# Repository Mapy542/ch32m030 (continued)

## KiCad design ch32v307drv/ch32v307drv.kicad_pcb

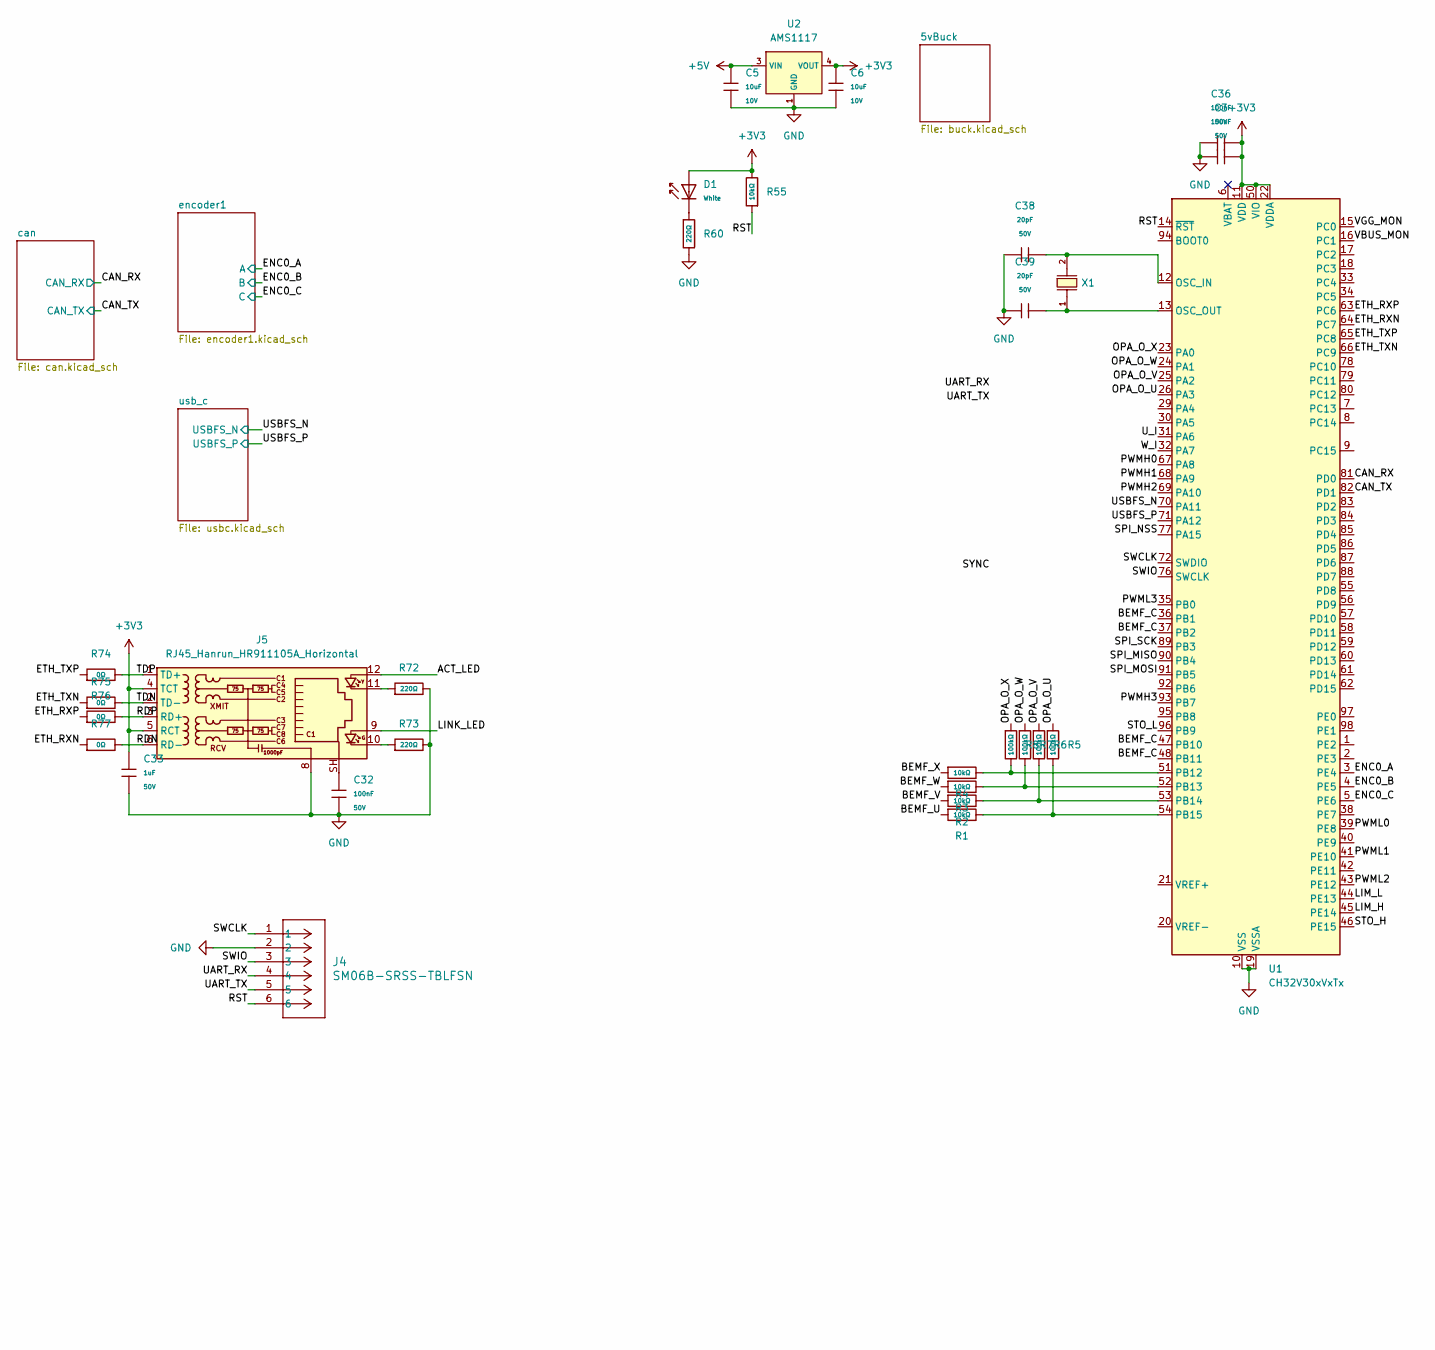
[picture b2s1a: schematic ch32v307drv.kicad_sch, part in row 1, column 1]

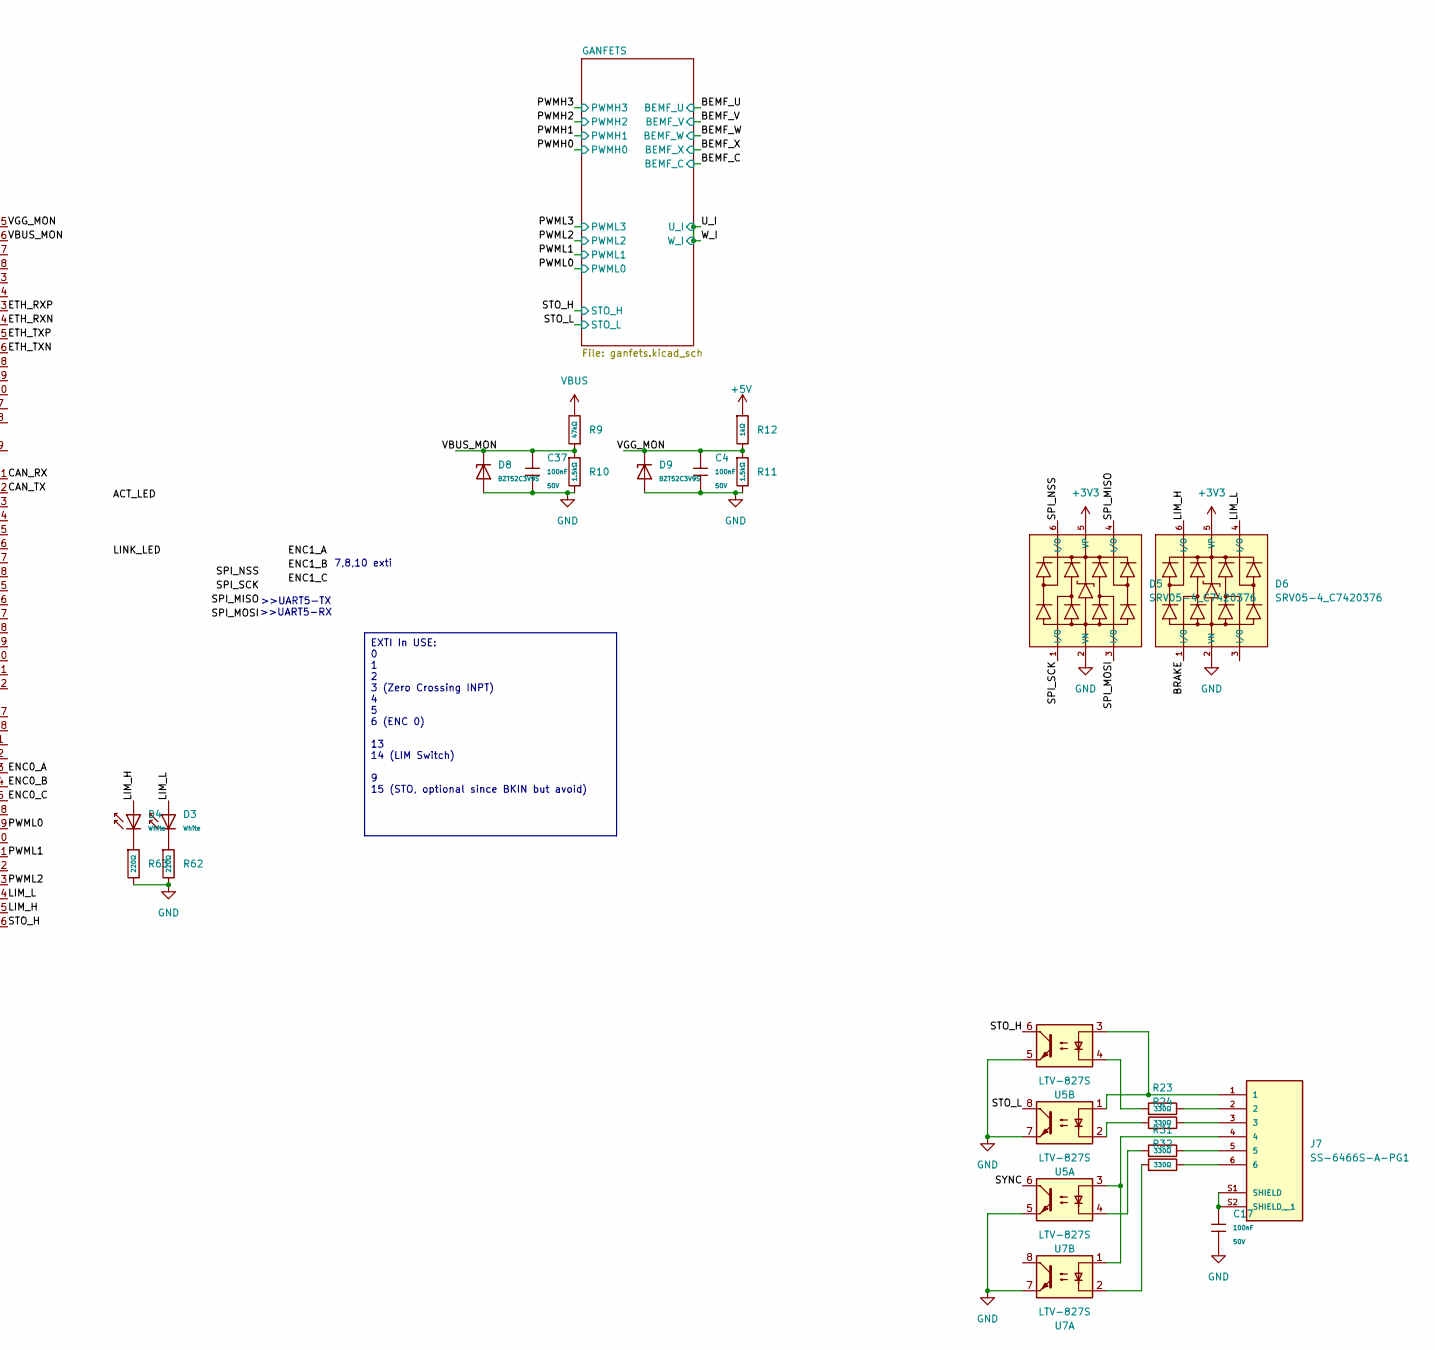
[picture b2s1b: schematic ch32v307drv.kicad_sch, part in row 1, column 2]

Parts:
C3, C4, C36, C37: 100nF; C_0603; Voltage Rated 50V; Tolerance ±10%; Part CC0603KRX7R9BB104; LCSC C14663
C5, C6: 10uF; C_0603; Voltage Rated 10V; Tolerance ±10%; Part CL10A106KP8NNNC; LCSC C19702
C17, C32: 100nF; C_1206; Voltage Rated 50V; Tolerance ±10%; Part CL31B104KBCNNNC; LCSC C24497
C33: 1uF; C_0603; Voltage Rated 50V; Tolerance ±10%; Part CL10A105KB8NNNC; LCSC C15849
C38, C39: 20pF; C_0402; Voltage Rated 50V; Tolerance ±5%; Part 0402CG200J500NT; LCSC C1554
D1, D3, D4: White; D_0603; Part KT-0603W; LCSC C2290
D5, D6: SRV05-4_C7420376; SOT-23-6_L2.9-W1.6-P0.95-LS2.8-BL-1; Breakdown Voltage (Vbr) 6V; Clamping Voltage@Ipp 12.5V; Part SRV05-4; LCSC C7420376
D8, D9: BZT52C3V9S; D_SOD-323; Part BZT52C3V9S; LCSC C22375299
J4: SM06B-SRSS-TBLFSN; CONN_SM06B-SRSS-TB_JST
J5: RJ45_Hanrun_HR911105A_Horizontal
J7: SS-6466S-A-PG1; BEL_SS-6466S-A-PG1; PARTREV A5
R1, R2, R3, R4, R55: 10kΩ; R_0603; Overload Voltage (Max) 75V; Tolerance ±1%; Part 0603WAF1002T5E; LCSC C25804
R5, R6, R7, R8: 100kΩ; R_0603; Overload Voltage (Max) 75V; Tolerance ±1%; Part 0603WAF1003T5E; LCSC C25803
R9: 47kΩ; R_0603; Overload Voltage (Max) 75V; Tolerance ±1%; Part 0603WAF4702T5E; LCSC C25819
R10, R11: 1.5kΩ; R_0603; Overload Voltage (Max) 75V; Tolerance ±1%; Part 0603WAF1501T5E; LCSC C22843
R12: 1kΩ; R_0603; Overload Voltage (Max) 75V; Tolerance ±1%; Part 0603WAF1001T5E; LCSC C21190
R23, R24, R31, R32: 330Ω; R_0603; Overload Voltage (Max) 75V; Tolerance ±1%; Part 0603WAF3300T5E; LCSC C23138
R60, R62, R63, R72, R73: 220Ω; R_0603; Overload Voltage (Max) 75V; Tolerance ±1%; Part 0603WAF2200T5E; LCSC C22962
R74, R75, R76, R77: 0Ω; R_0603; Overload Voltage (Max) 75V; Tolerance ±1%; Part 0603WAF0000T5E; LCSC C21189
U1: CH32V30xVxTx; LQFP-100_14x14mm_P0.5mm
U2: AMS1117; SOT-223-3_L6.5-W3.4-P2.30-LS7.0-BR; Output Voltage 3.3V; Dropout Voltage 1.3V@(800mA); Part AMS1117-3.3; LCSC C6186
U5, U7: LTV-827S; SMDIP-8_W9.53mm
X1: X50328MSB2GI; CRYSTAL-SMD_L5.0-W3.2; Frequency Tolerance ±10ppm; Part X50328MSB2GI; LCSC C115962

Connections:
+3V3: C3.2, C6.1, C33.1, C36.2, D1.2, D5.5 (VP), D6.5 (VP), J5.4 (TCT), J5.5 (RCT), R55.2, U1.11 (VDD), U1.22 (VDDA), U1.28 (VDD), U1.50 (VIO), U1.75 (VDD), U1.100 (VIO), U2.2 (VOUT), U2.4 (VOUT); also elsewhere on the board
+5V: C5.1, R12.1, U2.3 (VIN); also elsewhere on the board
/ACT_LED: J5.12
/BEMF_C: U1.36 (PB1), U1.37 (PB2), U1.47 (PB10), U1.48 (PB11); also elsewhere on the board
/BEMF_U: R1.1; also elsewhere on the board
/BEMF_V: R2.1; also elsewhere on the board
/BEMF_W: R3.1; also elsewhere on the board
/BEMF_X: R4.1; also elsewhere on the board
/BRAKE: D6.1 (I/O)
/CAN_RX: U1.81 (PD0); also elsewhere on the board
/CAN_TX: U1.82 (PD1); also elsewhere on the board
/ENC0_A: U1.3 (PE4); also elsewhere on the board
/ENC0_B: U1.4 (PE5); also elsewhere on the board
/ENC0_C: U1.5 (PE6); also elsewhere on the board
/ETH_RXN: R77.1, U1.64 (PC7)
/ETH_RXP: R76.1, U1.63 (PC6)
/ETH_TXN: R75.1, U1.66 (PC9)
/ETH_TXP: R74.1, U1.65 (PC8)
/LIM_H: D4.2, D6.6 (I/O), U1.45 (PE14)
/LIM_L: D3.2, D6.4 (I/O), U1.44 (PE13)
/LINK_LED: J5.9
/OPA_O_U: R5.1, U1.26 (PA3)
/OPA_O_V: R6.1, U1.25 (PA2)
/OPA_O_W: R7.1, U1.24 (PA1)
/OPA_O_X: R8.1, U1.23 (PA0)
/PWMH0: U1.67 (PA8); also elsewhere on the board
/PWMH1: U1.68 (PA9); also elsewhere on the board
/PWMH2: U1.69 (PA10); also elsewhere on the board
/PWMH3: U1.93 (PB7); also elsewhere on the board
/PWML0: U1.39 (PE8); also elsewhere on the board
/PWML1: U1.41 (PE10); also elsewhere on the board
/PWML2: U1.43 (PE12); also elsewhere on the board
/PWML3: U1.35 (PB0); also elsewhere on the board
/RDN: J5.6 (RD-), R77.2
/RDP: J5.3 (RD+), R76.2
/RST: J4.6, R55.1, U1.14 (~RST)
/SPI_MISO: D5.4 (I/O), U1.90 (PB4)
/SPI_MOSI: D5.3 (I/O), U1.91 (PB5)
/SPI_NSS: D5.6 (I/O), U1.77 (PA15)
/SPI_SCK: D5.1 (I/O), U1.89 (PB3)
/STO_H: U1.46 (PE15), U5.6; also elsewhere on the board
/STO_L: U1.96 (PB9), U5.8; also elsewhere on the board
/SWCLK: J4.1, U1.72 (SWDIO)
/SWIO: J4.3, U1.76 (SWCLK)
/SYNC: U7.6
/TDN: J5.2 (TD-), R75.2
/TDP: J5.1 (TD+), R74.2
/UART_RX: J4.4
/UART_TX: J4.5
/USBFS_N: U1.70 (PA11); also elsewhere on the board
/USBFS_P: U1.71 (PA12); also elsewhere on the board
/U_I: U1.31 (PA6), U1.32 (PA7); also elsewhere on the board
/VBUS_MON: C37.2, D8.1, R9.1, R10.1, U1.16 (PC1)
/VGG_MON: C4.2, D9.1, R11.1, R12.2, U1.15 (PC0)
GND: C3.1, C4.1, C5.2, C6.2, C17.2, C32.2, C33.2, C36.1, C37.1, C38.1, C39.1, D5.2 (VN), D6.2 (VN), D8.2, D9.2, J4.2, J5.8, R10.2, R11.2, R60.2, R62.2, R63.2, R72.2, R73.2, U1.10 (VSS), U1.19 (VSSA), U1.27 (VSS), U1.49 (VSS), U1.74 (VSS), U1.99 (VSS), U2.1 (GND), U5.5, U5.7, U7.5, U7.7; also elsewhere on the board
unnamed: C32.1, J5.SH
unnamed: D1.1, R60.1
unnamed: D3.1, R62.1
unnamed: D4.1, R63.1
unnamed: J5.10, R73.1
unnamed: J5.11, R72.1
unnamed: J7.1, U5.1, U5.3
unnamed: J7.2, R23.2
unnamed: J7.3, R24.2
unnamed: J7.4, U7.1, U7.3
unnamed: J7.5, R31.2
unnamed: J7.6, R32.2
unnamed: C17.1, J7.S1 (SHIELD), J7.S2 (SHIELD__1)
unnamed: R23.1, U5.4
unnamed: R24.1, U5.2
unnamed: R31.1, U7.4
unnamed: R32.1, U7.2
unnamed: C38.2, U1.12 (OSC_IN), U1.73 (NC), X1.2
unnamed: C39.2, U1.13 (OSC_OUT), X1.1
unnamed: R4.2, R8.2, U1.51 (PB12)
unnamed: R3.2, R7.2, U1.52 (PB13)
unnamed: R2.2, R6.2, U1.53 (PB14)
unnamed: R1.2, R5.2, U1.54 (PB15)
VBUS: R9.2; also elsewhere on the board

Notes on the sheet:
EXTI In USE: 0 1 2 3 (Zero Crossing INPT) 4 5 6 (ENC 0) 13 14 (LIM Switch) 9 15 (STO, optional since BKIN but avoid)
7,8,10 exti
>>UART5-TX >>UART5-RX

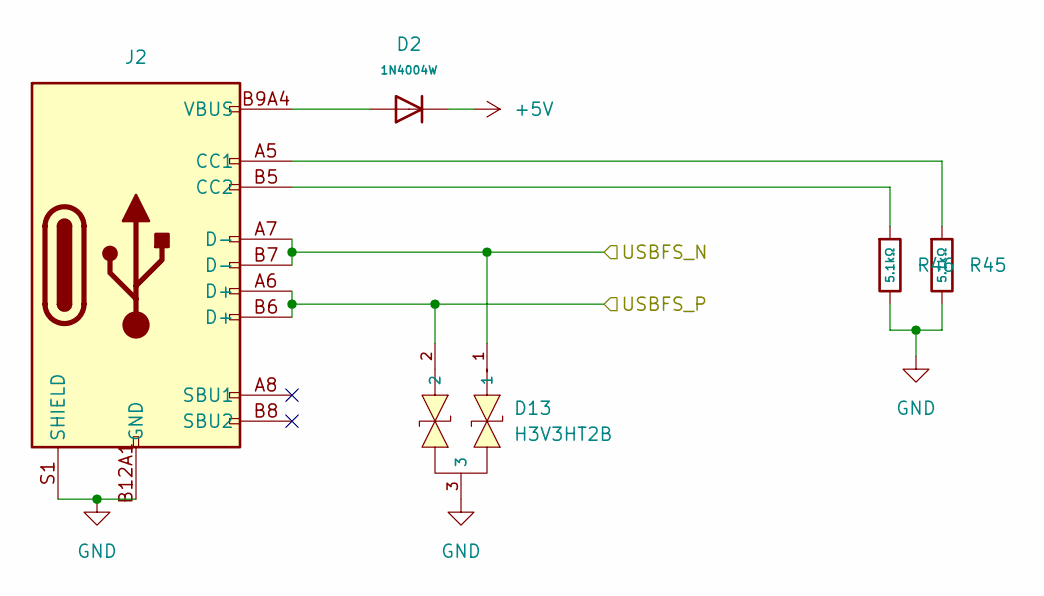
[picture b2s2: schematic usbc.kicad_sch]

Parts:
D2: 1N4004W; D_SOD-123FL; Forward Voltage (Vf@If) 1V@1.0A; Reverse Voltage (Vr) 400V; Part 1N4004W; LCSC C18199087
D13: H3V3HT2B; SOT-23-3_L2.9-W1.3-P1.90-LS2.4-BR; Part H3V3HT2B; LCSC C20617923
J2: Connector, USB-TYPE-C-16P; TYPE-C-SMD_HX-TYPE-C-16PIN; LCSC C2927039
R45, R46: 5.1kΩ; R_0603; Overload Voltage (Max) 75V; Tolerance ±1%; Part 0603WAF5101T5E; LCSC C23186

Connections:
+5V: D2.1; also elsewhere on the board
/USBFS_N: D13.1, J2.A7 (D-), J2.B7 (D-); also elsewhere on the board
/USBFS_P: D13.2, J2.A6 (D+), J2.B6 (D+); also elsewhere on the board
GND: D13.3, J2.A12B1 (GND), J2.B12A1 (GND), J2.S1 (SHIELD), R45.2, R46.2; also elsewhere on the board
unnamed: D2.2, J2.A9B4 (VBUS), J2.B9A4 (VBUS)
unnamed: J2.A5 (CC1), R45.1
unnamed: J2.B5 (CC2), R46.1

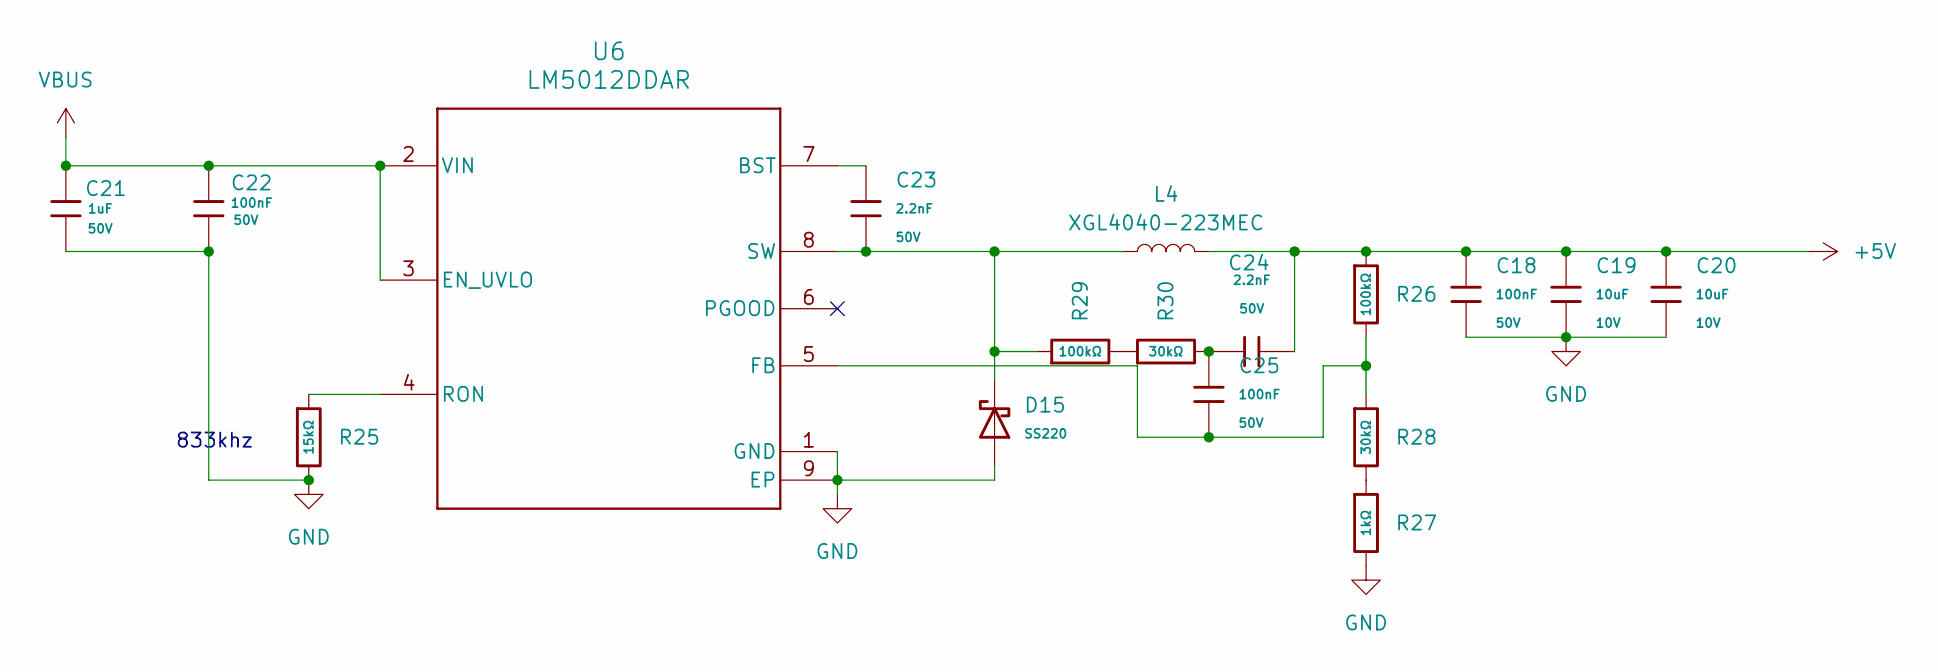
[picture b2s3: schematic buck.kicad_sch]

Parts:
C18, C25: 100nF; C_0603; Voltage Rated 50V; Tolerance ±10%; Part CC0603KRX7R9BB104; LCSC C14663
C19, C20: 10uF; C_0603; Voltage Rated 10V; Tolerance ±10%; Part CL10A106KP8NNNC; LCSC C19702
C21: 1uF; C_1206; Voltage Rated 50V; Tolerance ±10%; Part CL31B104KBCNNNC; LCSC C24497
C22: 100nF; C_1206; Voltage Rated 50V; Tolerance ±10%; Part CL31B104KBCNNNC; LCSC C24497
C23, C24: 2.2nF; C_0603; Voltage Rated 50V; Tolerance ±10%; Part 0603B222K500NT; LCSC C1604
D15: SS220; D_SMA; Forward Voltage (Vf@If) 0.95V@2.0A; Reverse Voltage (Vr) 200V; Part SS220; LCSC C7420361
L4: XGL4040-223MEC; L_Coilcraft_XAL4040-XXX
R25: 15kΩ; R_0603; Overload Voltage (Max) 75V; Tolerance ±1%; Part 0603WAF1502T5E; LCSC C22809
R26, R29: 100kΩ; R_0603; Overload Voltage (Max) 75V; Tolerance ±1%; Part 0603WAF1003T5E; LCSC C25803
R27: 1kΩ; R_0603; Overload Voltage (Max) 75V; Tolerance ±1%; Part 0603WAF1001T5E; LCSC C21190
R28, R30: 30kΩ; R_0603; Overload Voltage (Max) 75V; Tolerance ±1%; Part 0603WAF3002T5E; LCSC C22984
U6: LM5012DDAR; DDA0008E-MFG

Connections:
+5V: C18.1, C19.1, C20.1, C24.2, L4.2, R26.1; also elsewhere on the board
GND: C18.2, C19.2, C20.2, C21.1, C22.1, D15.2, R25.2, R27.2, U6.1 (GND), U6.9 (EP); also elsewhere on the board
unnamed: C24.1, C25.1, R30.2
unnamed: R27.1, R28.2
unnamed: R29.2, R30.1
unnamed: C23.1, U6.7 (BST)
unnamed: C25.2, R26.2, R28.1, U6.5 (FB)
unnamed: R25.1, U6.4 (RON)
unnamed: C23.2, D15.1, L4.1, R29.1, U6.8 (SW)
VBUS: C21.2, C22.2, U6.2 (VIN), U6.3 (EN_UVLO); also elsewhere on the board

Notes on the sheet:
833khz

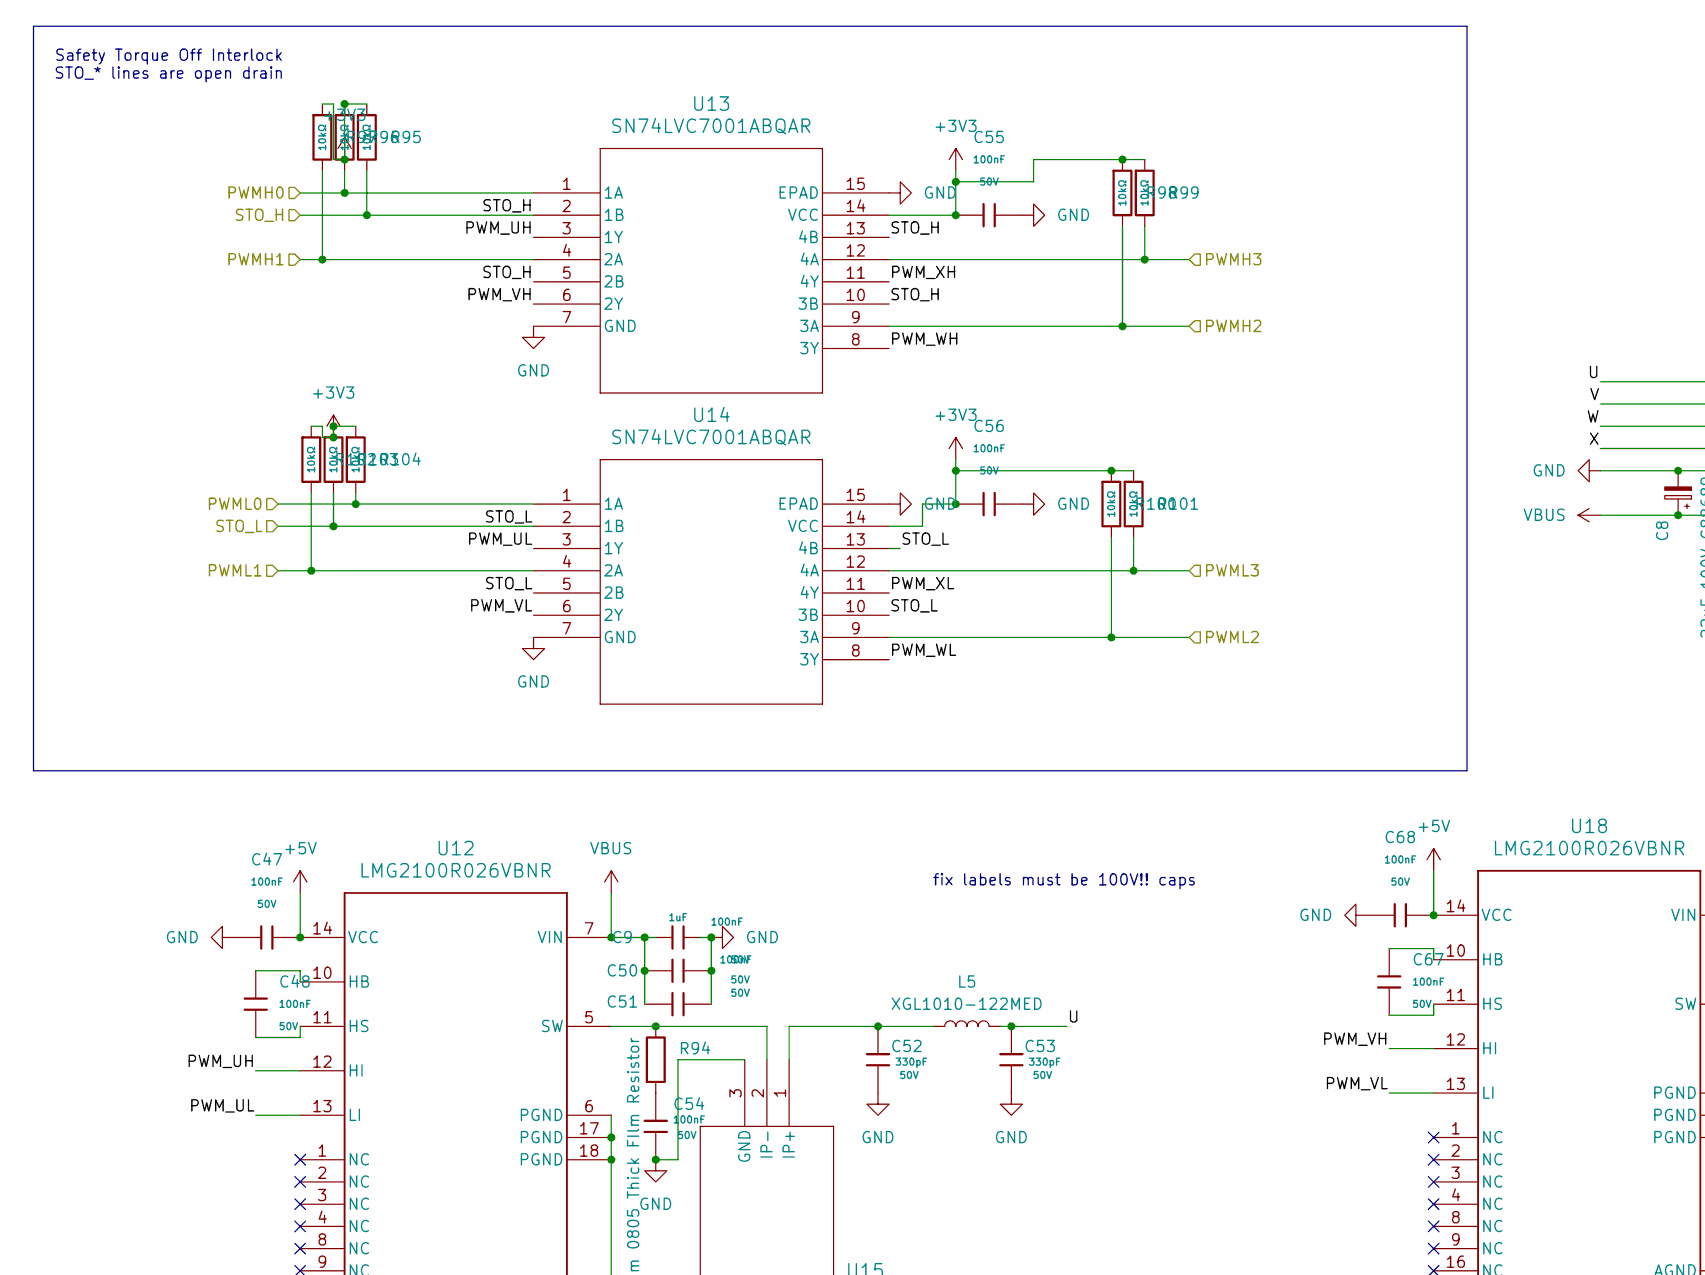
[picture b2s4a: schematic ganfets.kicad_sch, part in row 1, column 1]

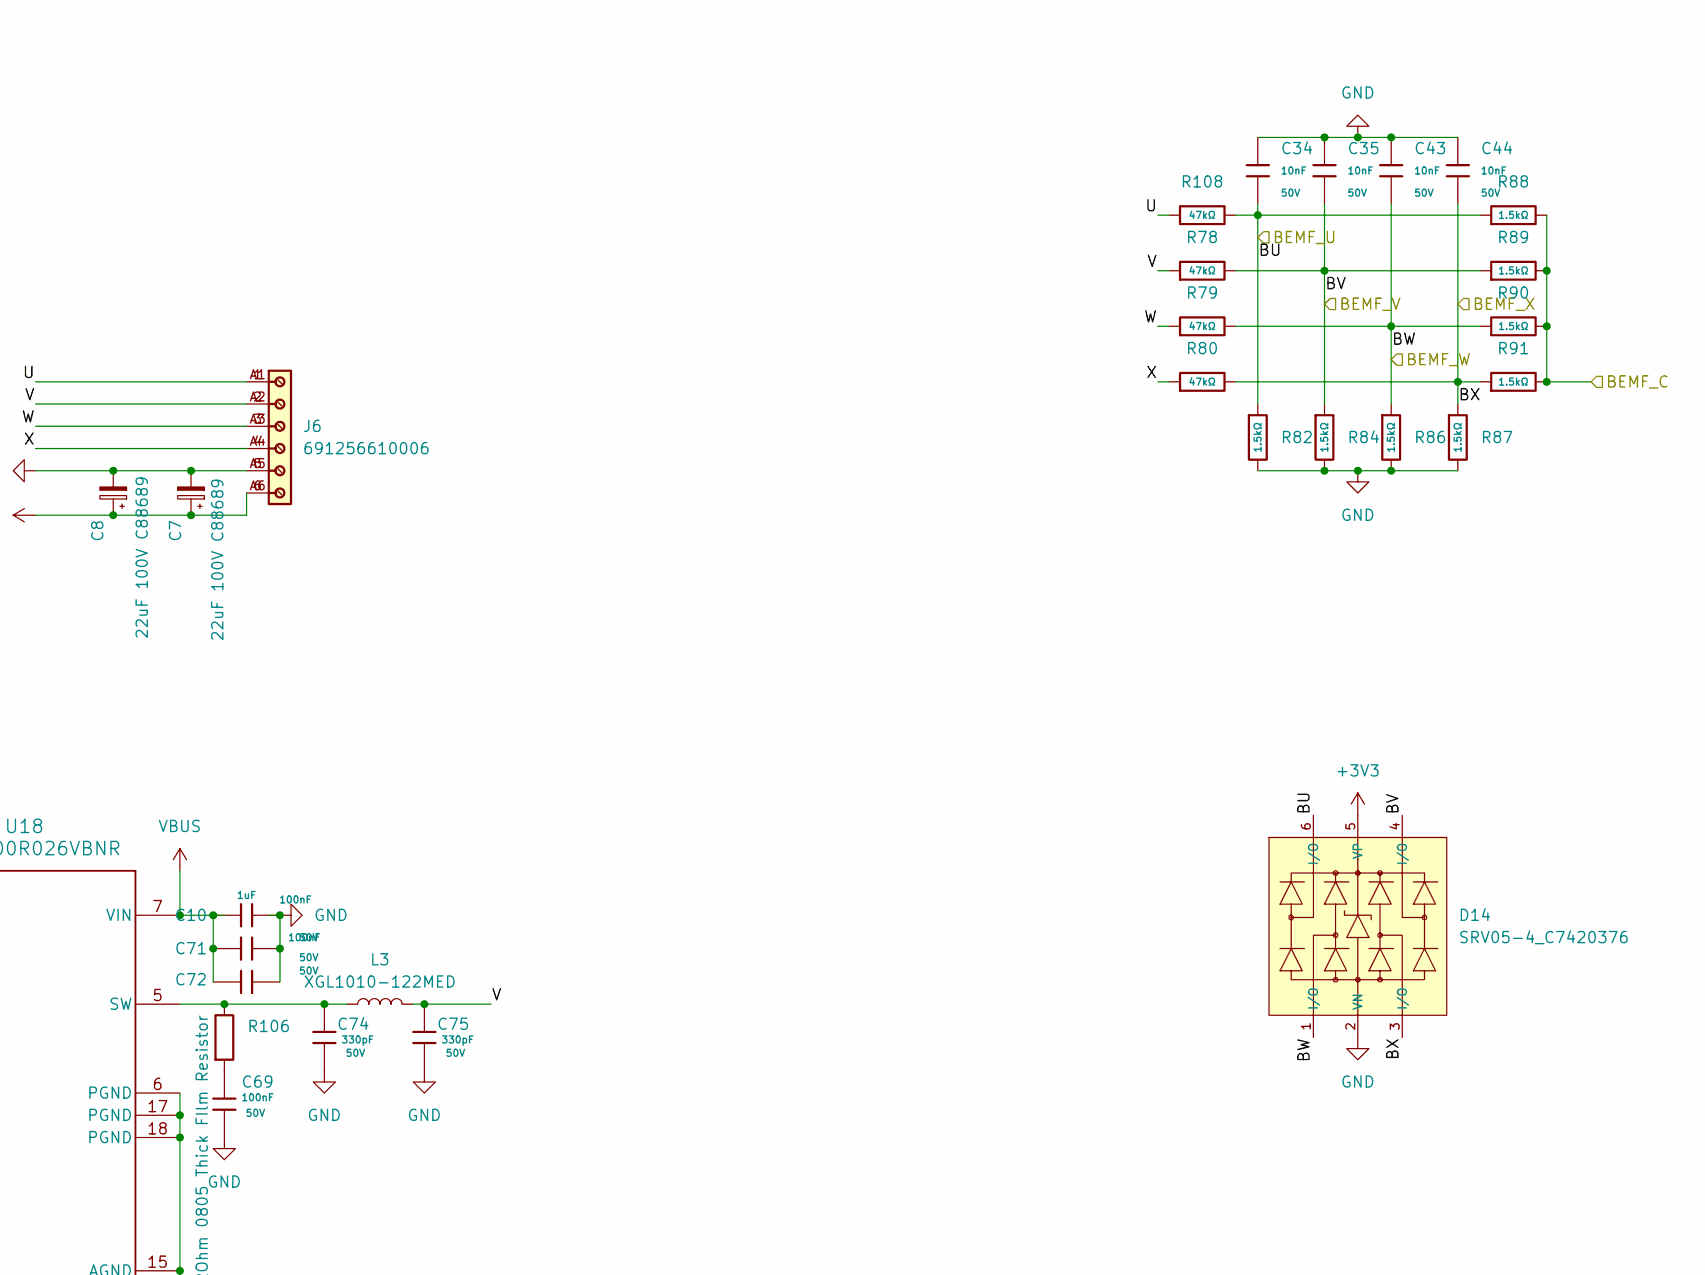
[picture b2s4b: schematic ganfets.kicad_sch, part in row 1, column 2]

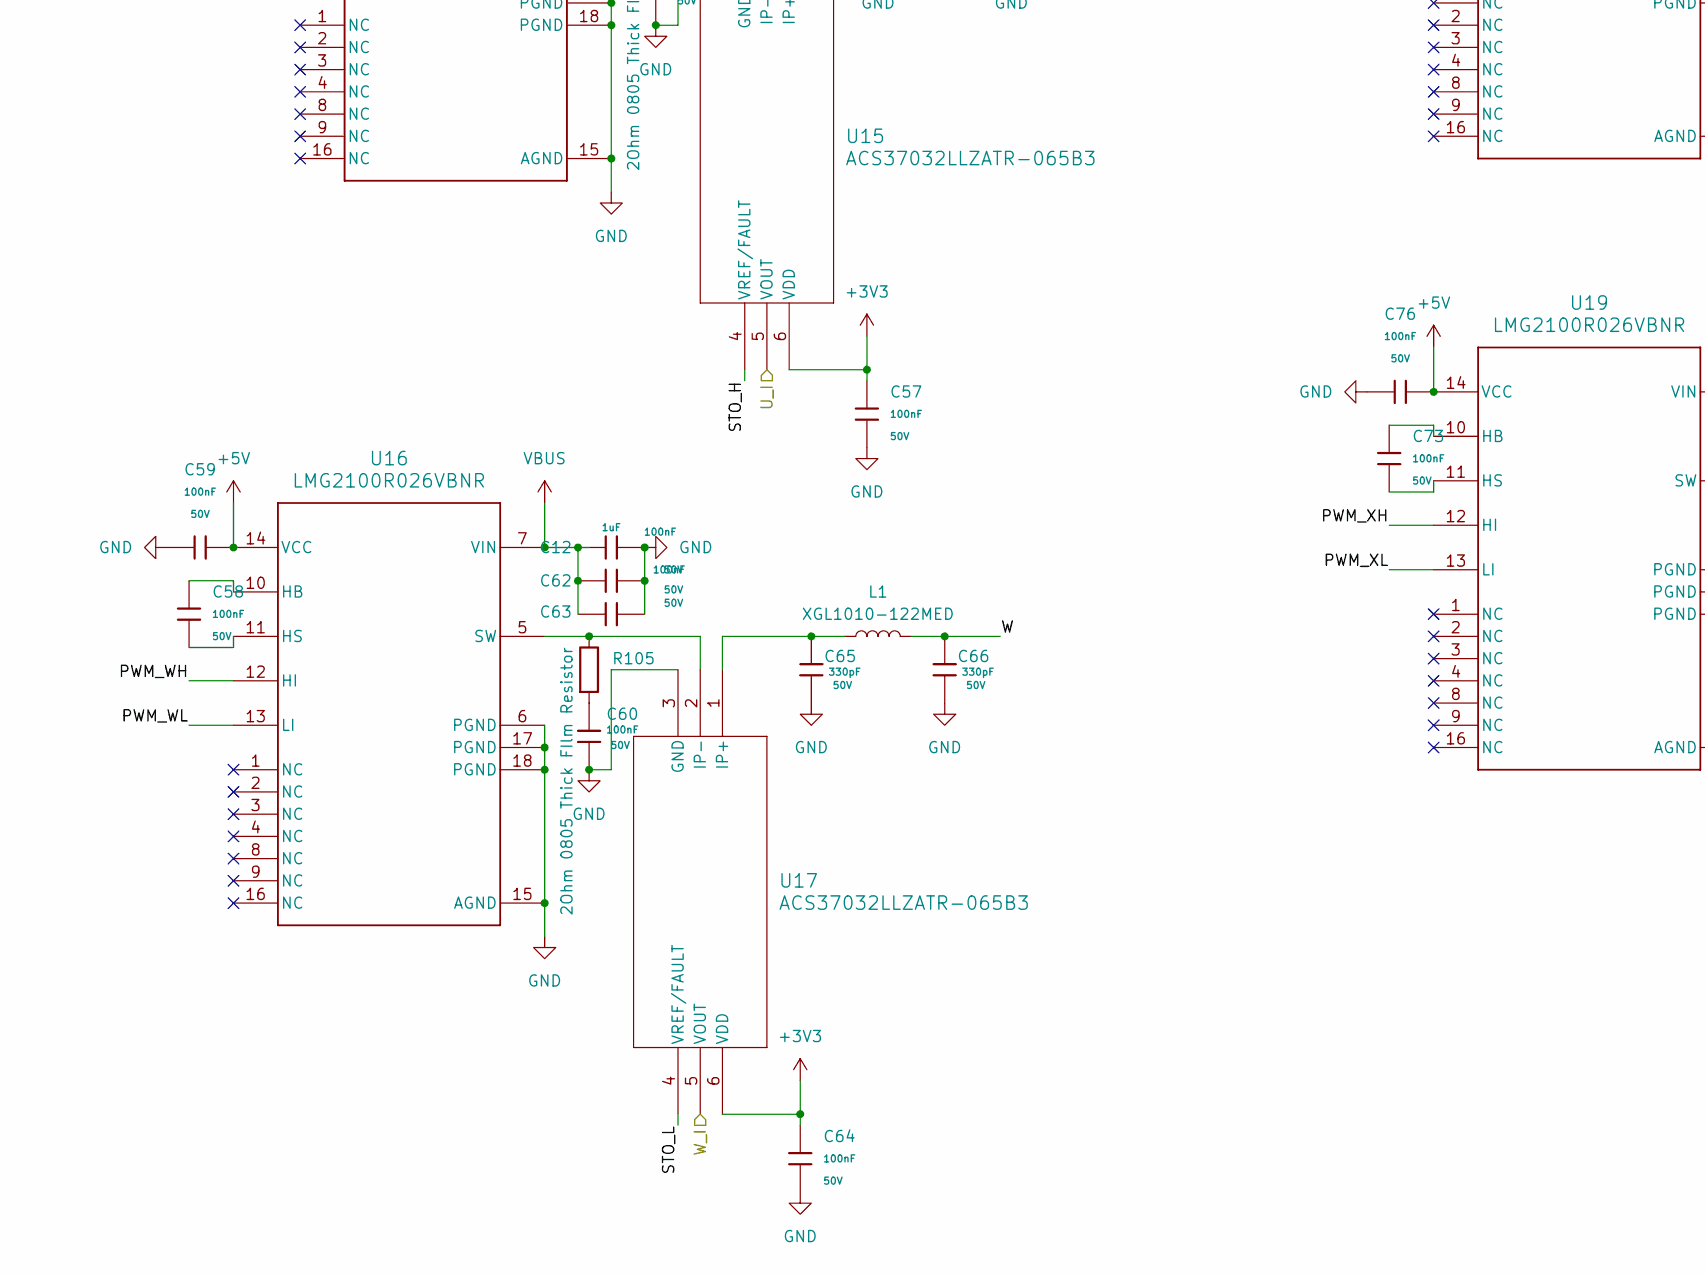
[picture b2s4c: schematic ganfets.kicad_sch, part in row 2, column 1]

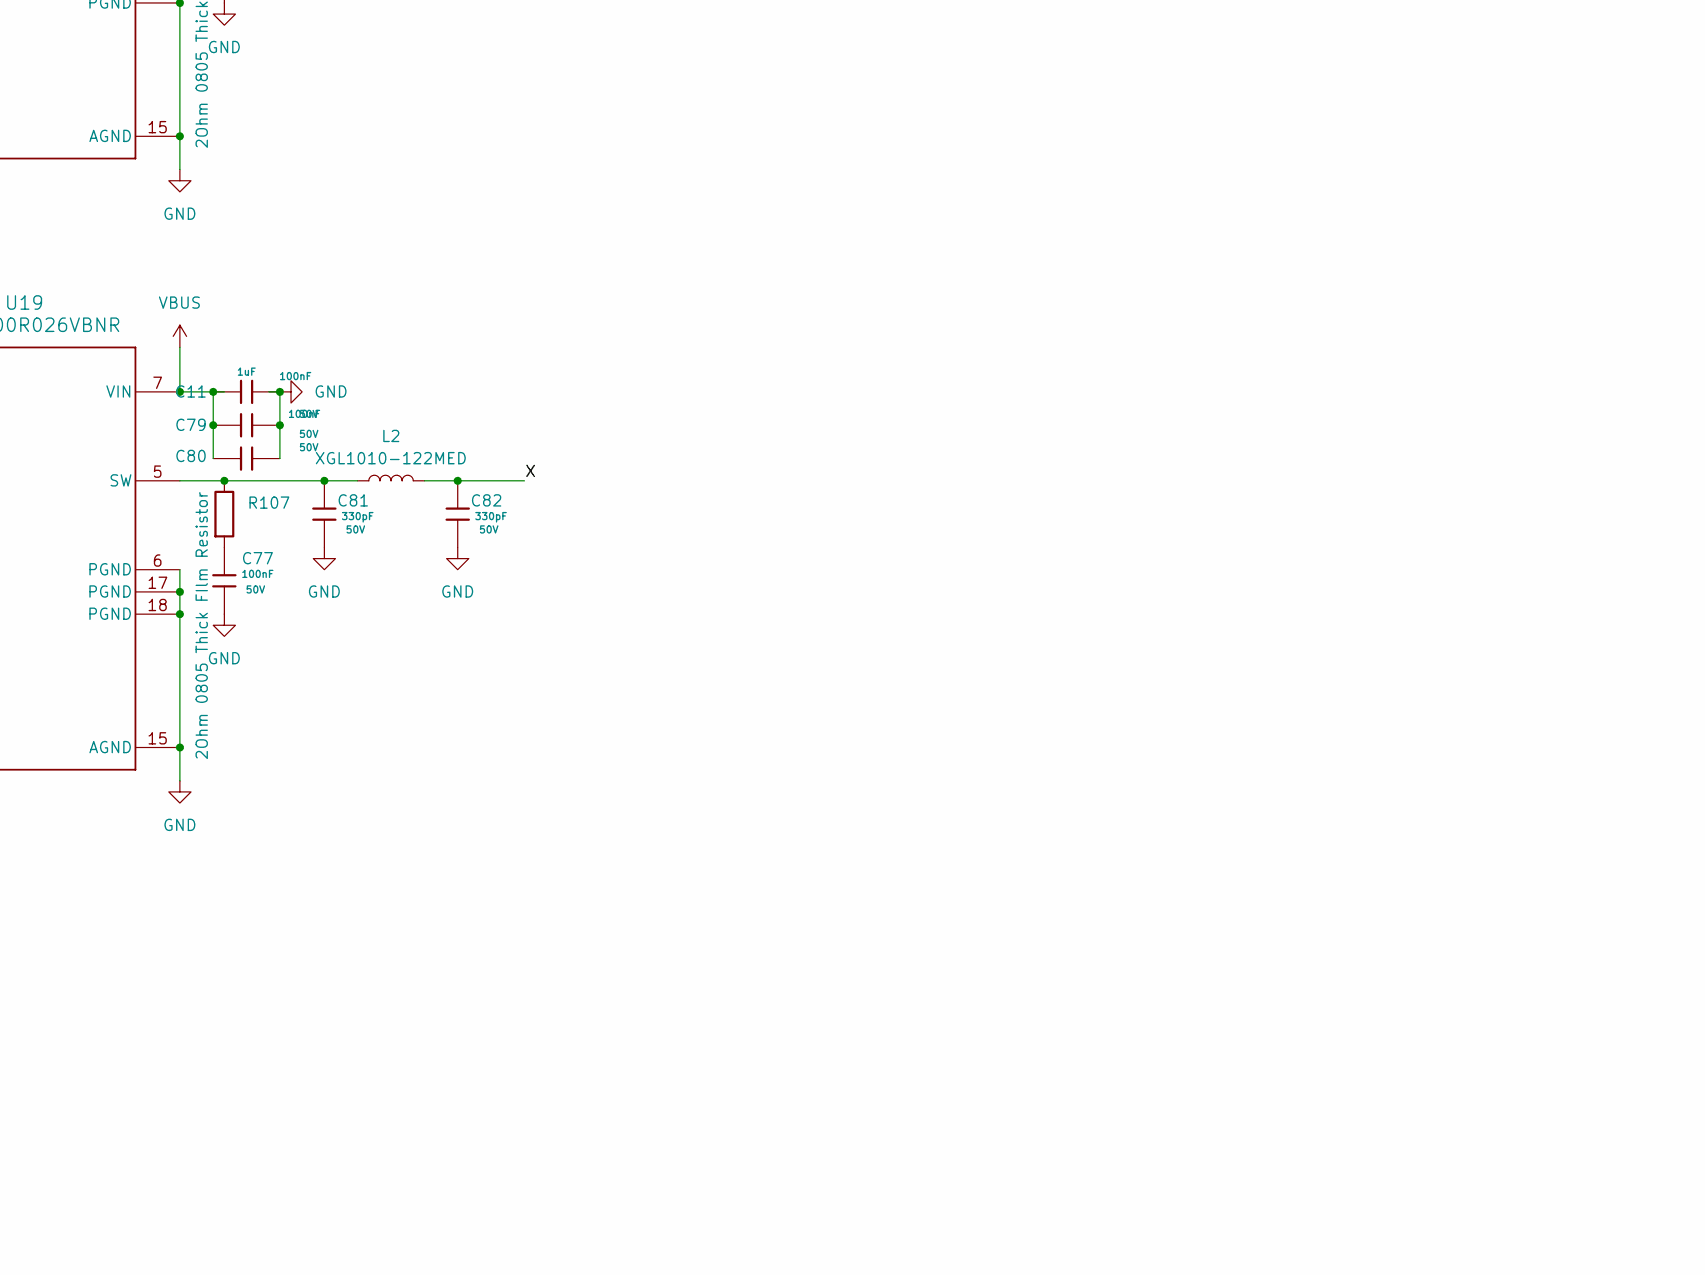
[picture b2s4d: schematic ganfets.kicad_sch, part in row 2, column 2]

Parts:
C7, C8: 22uF 100V C88689; CP_Elec_10x10
C9, C10, C11, C12: 1uF; C_1206; Voltage Rated 50V; Tolerance ±10%; Part CL31B104KBCNNNC; LCSC C24497
C34, C35, C43, C44: 10nF; C_0603; Voltage Rated 50V; Tolerance ±10%; Part 0603B103K500NT; LCSC C57112
C47, C48, C55, C56, C57, C58, C59, C64, C67, C68, C73, C76: 100nF; C_0603; Voltage Rated 50V; Tolerance ±10%; Part CC0603KRX7R9BB104; LCSC C14663
C50, C51, C54, C60, C62, C63, C69, C71, C72, C77, C79, C80: 100nF; C_1206; Voltage Rated 50V; Tolerance ±10%; Part CL31B104KBCNNNC; LCSC C24497
C52, C53, C65, C66, C74, C75, C81, C82: 330pF; C_1206; Voltage Rated 50V; Tolerance ±10%; Part CL31B104KBCNNNC; LCSC C24497
D14: SRV05-4_C7420376; SOT-23-6_L2.9-W1.6-P0.95-LS2.8-BL-1; Breakdown Voltage (Vbr) 6V; Clamping Voltage@Ipp 12.5V; Part SRV05-4; LCSC C7420376
J6: 691256610006
L1, L2, L3, L5: XGL1010-122MED; L_Coilcraft_XAL1010-XXX
R78, R79, R80, R108: 47kΩ; R_0603; Overload Voltage (Max) 75V; Tolerance ±1%; Part 0603WAF4702T5E; LCSC C25819
R82, R84, R86, R87, R88, R89, R90, R91: 1.5kΩ; R_0603; Overload Voltage (Max) 75V; Tolerance ±1%; Part 0603WAF1501T5E; LCSC C22843
R94, R105, R106, R107: 2Ohm 0805 Thick FIlm Resistor; R_0805_2012Metric
R95, R96, R97, R98, R99, R100, R101, R102, R103, R104: 10kΩ; R_0603; Overload Voltage (Max) 75V; Tolerance ±1%; Part 0603WAF1002T5E; LCSC C25804
U12, U16, U18, U19: LMG2100R026VBNR; VBN0018A-MFG
U13, U14: SN74LVC7001ABQAR; PW14
U15, U17: ACS37032LLZATR-065B3; SOIC6_LZ_ALM

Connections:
+3V3: C55.2, C56.2, C57.1, C64.1, D14.5 (VP), R95.1, R96.1, R97.1, R98.1, R99.1, R100.1, R101.1, R102.1, R103.1, R104.1, U13.14 (VCC), U14.14 (VCC), U15.6 (VDD), U17.6 (VDD); also elsewhere on the board
+5V: C47.2, C59.2, C68.2, C76.2, U12.14 (VCC), U16.14 (VCC), U18.14 (VCC), U19.14 (VCC); also elsewhere on the board
/BEMF_C: R88.2, R89.2, R90.2, R91.2; also elsewhere on the board
/BEMF_U: C34.2, D14.6 (I/O), R82.1, R88.1, R108.2; also elsewhere on the board
/BEMF_V: C35.2, D14.4 (I/O), R78.2, R84.1, R89.1; also elsewhere on the board
/BEMF_W: C43.2, D14.1 (I/O), R79.2, R86.1, R90.1; also elsewhere on the board
/BEMF_X: C44.2, D14.3 (I/O), R80.2, R87.1, R91.1; also elsewhere on the board
/GANFETS/PWM_UH: U12.12 (HI), U13.3 (1Y)
/GANFETS/PWM_UL: U12.13 (LI), U14.3 (1Y)
/GANFETS/PWM_VH: U13.6 (2Y), U18.12 (HI)
/GANFETS/PWM_VL: U14.6 (2Y), U18.13 (LI)
/GANFETS/PWM_WH: U13.8 (3Y), U16.12 (HI)
/GANFETS/PWM_WL: U14.8 (3Y), U16.13 (LI)
/GANFETS/PWM_XH: U13.11 (4Y), U19.12 (HI)
/GANFETS/PWM_XL: U14.11 (4Y), U19.13 (LI)
/GANFETS/U: C53.1, J6.1, J6.A1, L5.2, R108.1
/GANFETS/V: C75.1, J6.2, J6.A2, L3.2, R78.1
/GANFETS/W: C66.1, J6.3, J6.A3, L1.2, R79.1
/GANFETS/X: C82.1, J6.4, J6.A4, L2.2, R80.1
/PWMH0: R96.2, U13.1 (1A); also elsewhere on the board
/PWMH1: R97.2, U13.4 (2A); also elsewhere on the board
/PWMH2: R98.2, U13.9 (3A); also elsewhere on the board
/PWMH3: R99.2, U13.12 (4A); also elsewhere on the board
/PWML0: R104.2, U14.1 (1A); also elsewhere on the board
/PWML1: R102.2, U14.4 (2A); also elsewhere on the board
/PWML2: R100.2, U14.9 (3A); also elsewhere on the board
/PWML3: R101.2, U14.12 (4A); also elsewhere on the board
/STO_H: R95.2, U13.2 (1B), U13.5 (2B), U13.10 (3B), U13.13 (4B), U15.4 (VREF/FAULT); also elsewhere on the board
/STO_L: R103.2, U14.2 (1B), U14.5 (2B), U14.10 (3B), U14.13 (4B), U17.4 (VREF/FAULT); also elsewhere on the board
/U_I: U15.5 (VOUT), U17.5 (VOUT); also elsewhere on the board
GND: C7.2, C8.2, C9.2, C10.2, C11.2, C12.2, C34.1, C35.1, C43.1, C44.1, C47.1, C50.2, C51.2, C52.2, C53.2, C54.2, C55.1, C56.1, C57.2, C59.1, C60.2, C62.2, C63.2, C64.2, C65.2, C66.2, C68.1, C69.2, C71.2, C72.2, C74.2, C75.2, C76.1, C77.2, C79.2, C80.2, C81.2, C82.2, D14.2 (VN), J6.5, J6.A5, R82.2, R84.2, R86.2, R87.2, U12.6 (PGND), U12.15 (AGND), U12.17 (PGND), U12.18 (PGND), U13.7 (GND), U13.15 (EPAD), U14.7 (GND), U14.15 (EPAD), U15.3 (GND), U16.6 (PGND), U16.15 (AGND), U16.17 (PGND), U16.18 (PGND), U17.3 (GND), U18.6 (PGND), U18.15 (AGND), U18.17 (PGND), U18.18 (PGND), U19.6 (PGND), U19.15 (AGND), U19.17 (PGND), U19.18 (PGND); also elsewhere on the board
unnamed: C54.1, R94.2
unnamed: C60.1, R105.2
unnamed: C69.1, R106.2
unnamed: C77.1, R107.2
unnamed: C48.2, U12.10 (HB)
unnamed: C48.1, U12.11 (HS)
unnamed: R94.1, U12.5 (SW), U15.2 (IP-)
unnamed: C52.1, L5.1, U15.1 (IP+)
unnamed: C58.2, U16.10 (HB)
unnamed: C58.1, U16.11 (HS)
unnamed: R105.1, U16.5 (SW), U17.2 (IP-)
unnamed: C65.1, L1.1, U17.1 (IP+)
unnamed: C67.2, U18.10 (HB)
unnamed: C67.1, U18.11 (HS)
unnamed: C74.1, L3.1, R106.1, U18.5 (SW)
unnamed: C73.2, U19.10 (HB)
unnamed: C73.1, U19.11 (HS)
unnamed: C81.1, L2.1, R107.1, U19.5 (SW)
VBUS: C7.1, C8.1, C9.1, C10.1, C11.1, C12.1, C50.1, C51.1, C62.1, C63.1, C71.1, C72.1, C79.1, C80.1, J6.6, J6.A6, U12.7 (VIN), U16.7 (VIN), U18.7 (VIN), U19.7 (VIN); also elsewhere on the board

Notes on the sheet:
Safety Torque Off Interlock STO_* lines are open drain
fix labels must be 100V!! caps
